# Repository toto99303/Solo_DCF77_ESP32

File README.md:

# Solo DCF77 ESP32 transmitter
So what is this? It's a standalone DCF77 transmitter designed to be used with any wrist watch that is capable of receiving the signal. (Casio Wave Ceptor series etc.)

#### Features:
- Connects to your local WiFi network.
- Syncs the exact time via NTP and converts it to DCF77 signal.
- Shows the realtime data on the OLED display live.
- Uses screensavers to protect the screen from burn-in. (changes every minute)
- 3D printable stand.

### PCB and full BOM:

The original Eagle design files are included as well as exported GERBER files for direct PCB production.

BOM:
- 1 x ESP32-WROOM-32 barebone
- 1 x 7 Pin SPI 0.96" Dual Color Yellow Blue OLED Display Module SSD1306 (https://hacktronics.co.in/lcd-displays/7-pin-spi-iic-096-dual-color-yellow-blue-oled-display-module-ssd1306)
- 1 x Mini USB female vertical TH (https://store.comet.bg/download-file.php?id=18384)
- 1 x MCP1826S-3302E/DB voltage regulator (https://store.comet.bg/download-file.php?id=4147)
- 3 x TANT B SMD 22uF 16V caps
- 2 x C1206 100nF 50V caps
- 2 x R1206 10K resistors
- 2 x R1206 4.7K resistors
- 1 x R1206 560R resistor

### Firmware
To upload the sketch you will need USB to serial UART converter capable of supplying 3.3V VCC.
Pinout for the header:

Remember that in order to boot the EPS32 in programming mode you will need to connect GPIO0 pin to GND (Low).

1. Open the sketch in Arduino IDE and edit your wifi SSID and password.
2. Use board "WEMOS LOLIN32" at 80Mhz flash frequency. (Tools -> Board)
3. Compile and upload.

### 3D printable stand

The original design file from Fusion360 is available as well as ready to print STLs.

### Video:

### More Pictures:

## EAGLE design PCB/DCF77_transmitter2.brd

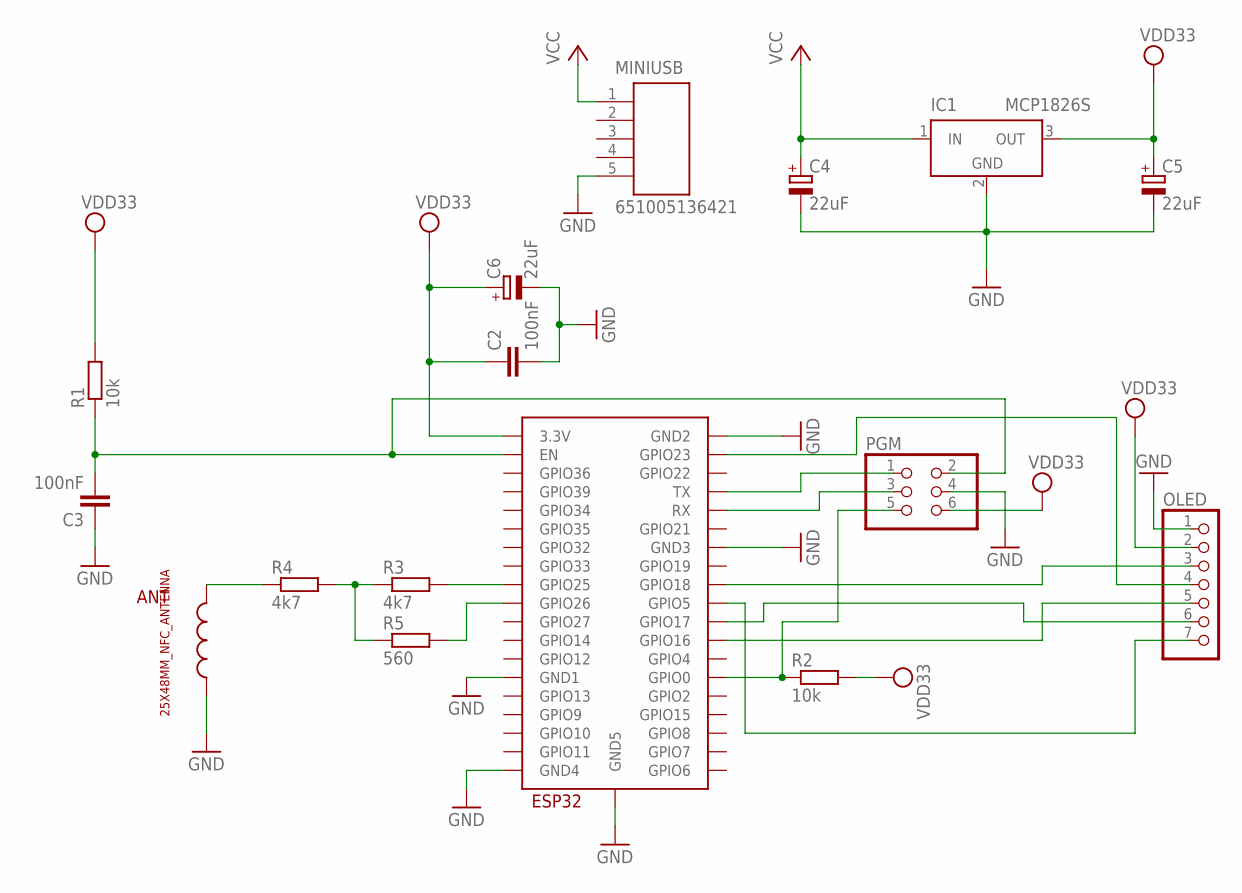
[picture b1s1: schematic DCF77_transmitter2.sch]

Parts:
ANT: 25X48MM_NFC_ANTENNA
C2, C3: 100nF; C1206
C4, C5, C6: 22uF; B/3528-21W
IC1: MCP1826S; SOT223
MINIUSB: 651005136421
OLED: PINHD-1X7; 1X07
PGM: PINHD-2X3; 2X03
R1, R2: 10k; R1206
R3, R4: 4k7; R1206
R5: 560; R1206
U$2: ESP32-WROOM

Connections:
EN: C3.2, PGM.2, R1.1, U$2.EN
GND: ANT.P$2, C2.2, C3.1, C4.-, C5.-, C6.-, IC1.2 (GND), IC1.4 (GND), MINIUSB.5, OLED.1, PGM.4, U$2.GND1, U$2.GND2, U$2.GND3, U$2.GND4, U$2.GND5
GPIO0: PGM.5, R2.1, U$2.IO0 (GPIO0)
GPIO5: OLED.7, U$2.IO5 (GPIO5)
GPIO16: OLED.5, U$2.IO16 (GPIO16)
GPIO17: OLED.6, U$2.IO17 (GPIO17)
GPIO18: OLED.3, U$2.IO18 (GPIO18)
GPIO23: OLED.4, U$2.IO23 (GPIO23)
unnamed: R5.2, U$2.IO26 (GPIO26)
unnamed: R3.2, U$2.IO25 (GPIO25)
unnamed: R3.1, R4.2, R5.1
unnamed: ANT.P$1, R4.1
RX: PGM.3, U$2.RX
TX: PGM.1, U$2.TX
VCC: C4.+, IC1.1 (IN), MINIUSB.1
VDD33: C2.1, C5.+, C6.+, IC1.3 (OUT), OLED.2, PGM.6, R1.2, R2.2, U$2.3V3 (3.3V)

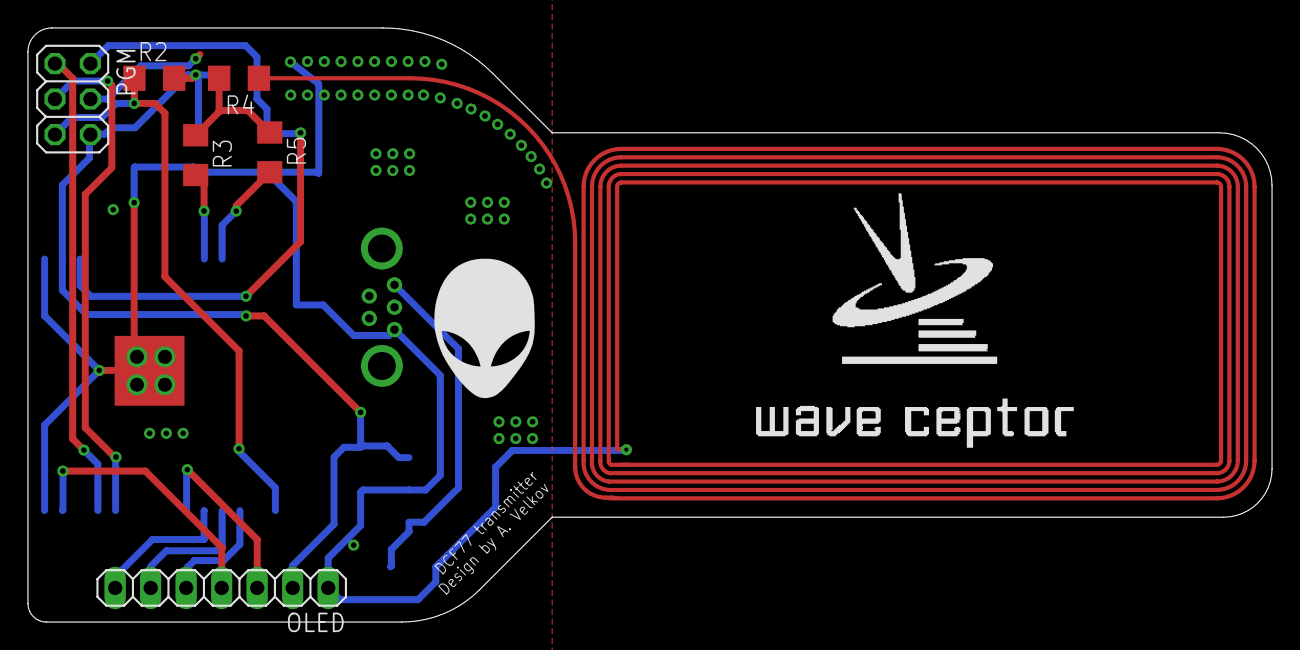
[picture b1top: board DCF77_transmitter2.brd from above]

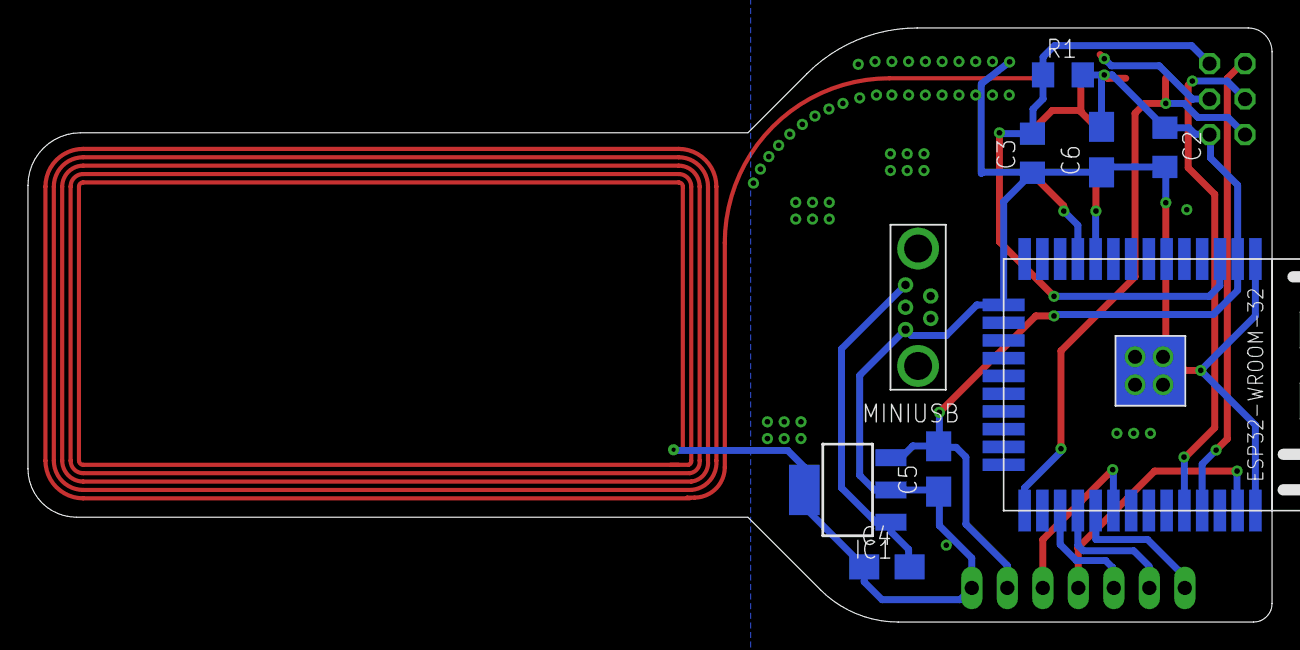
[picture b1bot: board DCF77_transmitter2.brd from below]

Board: 2 copper layers, 89.0 x 42.5 mm, 16 parts (9 on the bottom side), 16 nets.

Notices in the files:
parts and their libraries:
Wuerth_Elektronik_eiCan_Communication_Co: Copyright: Würth Elektronik
